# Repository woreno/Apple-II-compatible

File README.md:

# Apple-II-compatible (2021)
Ths is an Apple II compatible built from scratch. As it was made by transfer photo-paper and etching with ferric chloride, and made the traces wider to avoid errors; as result the board didn't fit the A4 copper sheet and memory and slots were made in 2 different boards. 
* The DRAM logic is a bit different from the original.
* System ROM halves are selectable by a switch; one half will run a memory test, another half is Apple II original ROM.
* Character ROM layout is different as pins differs.
* The keyboard and keyboard board were also etched, and theres a ROM that translates the scancodes into ascii - the original had a GY AY-5-3600 chip with a integrated ROM etched from factory.   
* It just has 4 slots instead of 8. Never tested a the slots as i have no Apple II cards. 
Despite this i had planned to assign a number to each of them using a small ROM to store them, and having 7-segment displays to display their number but this as too cumbersome and i stopped the project.

**References** 
 * The Apple II Circuit Description, 1983, Winston D. Gayler
 * Ben Eater's EEPROM arduino programmer

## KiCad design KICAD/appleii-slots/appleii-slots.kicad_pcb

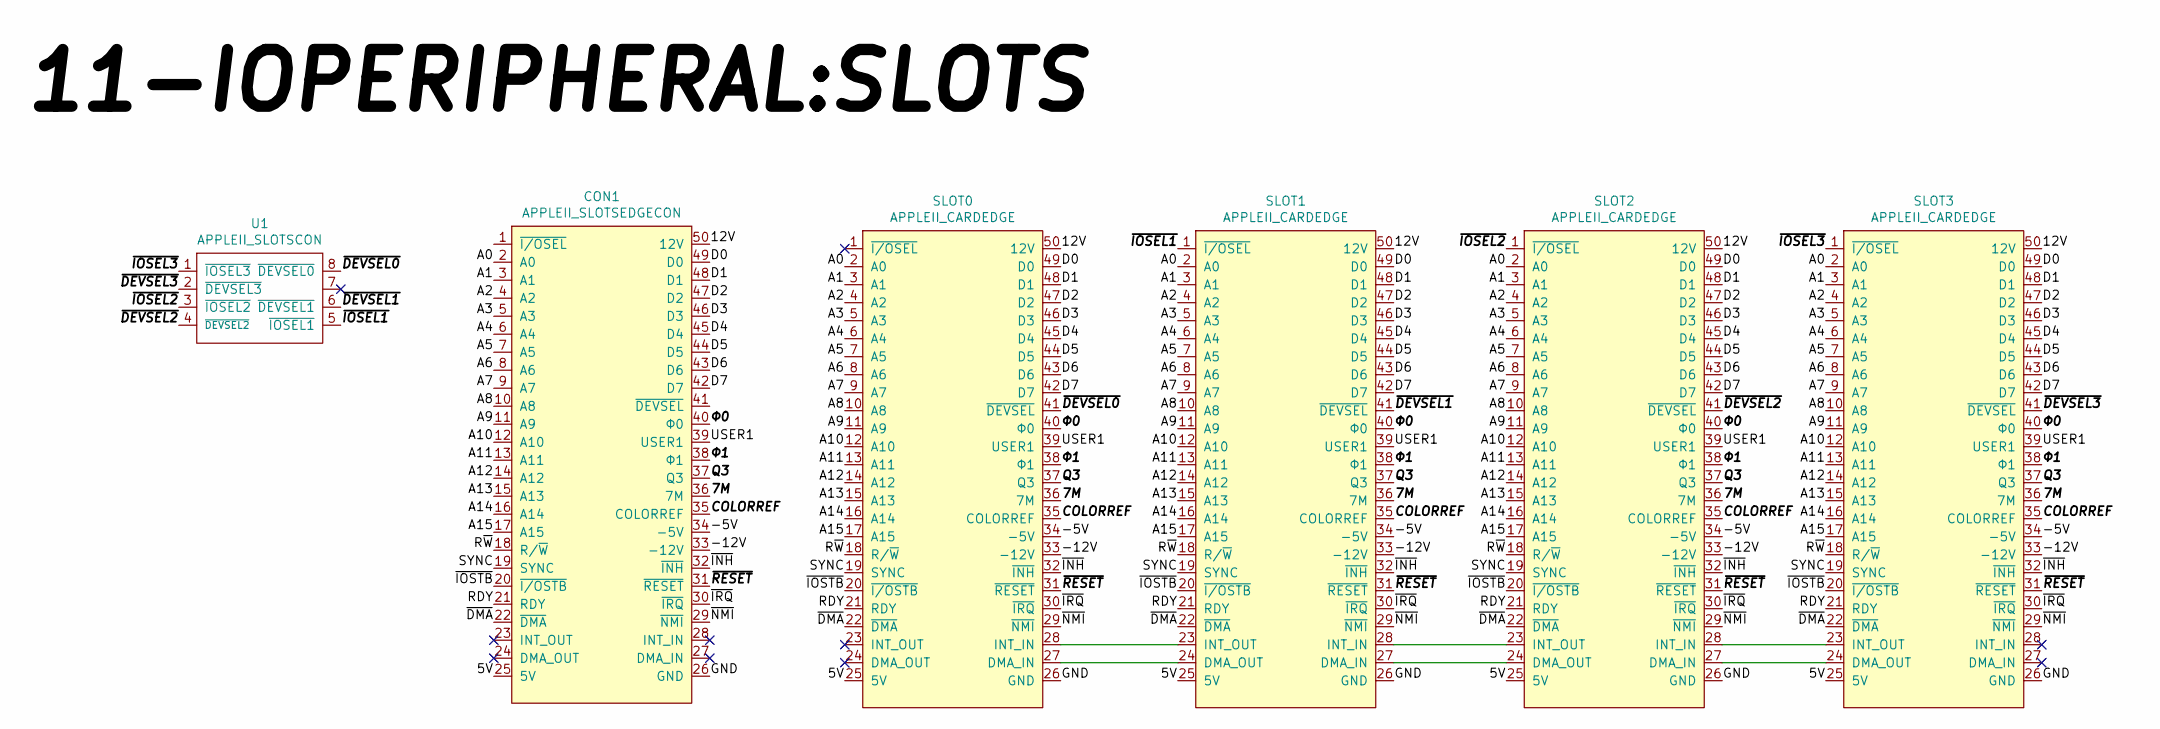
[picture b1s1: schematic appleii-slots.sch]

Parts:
CON1: APPLEII_SLOTSEDGECON; Apple_8bit_edge
SLOT0, SLOT1, SLOT2, SLOT3: APPLEII_CARDEDGE; Conector2x25_Oval_tinny
U1: APPLEII_SLOTSCON; conetor_2x04_P2.54

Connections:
/5V: CON1.25 (5V), SLOT0.25 (5V), SLOT1.25 (5V), SLOT2.25 (5V), SLOT3.25 (5V)
/7M: CON1.36 (7M), SLOT0.36 (7M), SLOT1.36 (7M), SLOT2.36 (7M), SLOT3.36 (7M)
/12V: CON1.50 (12V), SLOT0.50 (12V), SLOT1.50 (12V), SLOT2.50 (12V), SLOT3.50 (12V)
/-5V: CON1.34 (-5V), SLOT0.34 (-5V), SLOT1.34 (-5V), SLOT2.34 (-5V), SLOT3.34 (-5V)
/-12V: CON1.33 (-12V), SLOT0.33 (-12V), SLOT1.33 (-12V), SLOT2.33 (-12V), SLOT3.33 (-12V)
/A0: CON1.2 (A0), SLOT0.2 (A0), SLOT1.2 (A0), SLOT2.2 (A0), SLOT3.2 (A0)
/A1: CON1.3 (A1), SLOT0.3 (A1), SLOT1.3 (A1), SLOT2.3 (A1), SLOT3.3 (A1)
/A2: CON1.4 (A2), SLOT0.4 (A2), SLOT1.4 (A2), SLOT2.4 (A2), SLOT3.4 (A2)
/A3: CON1.5 (A3), SLOT0.5 (A3), SLOT1.5 (A3), SLOT2.5 (A3), SLOT3.5 (A3)
/A4: CON1.6 (A4), SLOT0.6 (A4), SLOT1.6 (A4), SLOT2.6 (A4), SLOT3.6 (A4)
/A5: CON1.7 (A5), SLOT0.7 (A5), SLOT1.7 (A5), SLOT2.7 (A5), SLOT3.7 (A5)
/A6: CON1.8 (A6), SLOT0.8 (A6), SLOT1.8 (A6), SLOT2.8 (A6), SLOT3.8 (A6)
/A7: CON1.9 (A7), SLOT0.9 (A7), SLOT1.9 (A7), SLOT2.9 (A7), SLOT3.9 (A7)
/A8: CON1.10 (A8), SLOT0.10 (A8), SLOT1.10 (A8), SLOT2.10 (A8), SLOT3.10 (A8)
/A9: CON1.11 (A9), SLOT0.11 (A9), SLOT1.11 (A9), SLOT2.11 (A9), SLOT3.11 (A9)
/A10: CON1.12 (A10), SLOT0.12 (A10), SLOT1.12 (A10), SLOT2.12 (A10), SLOT3.12 (A10)
/A11: CON1.13 (A11), SLOT0.13 (A11), SLOT1.13 (A11), SLOT2.13 (A11), SLOT3.13 (A11)
/A12: CON1.14 (A12), SLOT0.14 (A12), SLOT1.14 (A12), SLOT2.14 (A12), SLOT3.14 (A12)
/A13: CON1.15 (A13), SLOT0.15 (A13), SLOT1.15 (A13), SLOT2.15 (A13), SLOT3.15 (A13)
/A14: CON1.16 (A14), SLOT0.16 (A14), SLOT1.16 (A14), SLOT2.16 (A14), SLOT3.16 (A14)
/A15: CON1.17 (A15), SLOT0.17 (A15), SLOT1.17 (A15), SLOT2.17 (A15), SLOT3.17 (A15)
/COLORREF: CON1.35 (COLORREF), SLOT0.35 (COLORREF), SLOT1.35 (COLORREF), SLOT2.35 (COLORREF), SLOT3.35 (COLORREF)
/D0: CON1.49 (D0), SLOT0.49 (D0), SLOT1.49 (D0), SLOT2.49 (D0), SLOT3.49 (D0)
/D1: CON1.48 (D1), SLOT0.48 (D1), SLOT1.48 (D1), SLOT2.48 (D1), SLOT3.48 (D1)
/D2: CON1.47 (D2), SLOT0.47 (D2), SLOT1.47 (D2), SLOT2.47 (D2), SLOT3.47 (D2)
/D3: CON1.46 (D3), SLOT0.46 (D3), SLOT1.46 (D3), SLOT2.46 (D3), SLOT3.46 (D3)
/D4: CON1.45 (D4), SLOT0.45 (D4), SLOT1.45 (D4), SLOT2.45 (D4), SLOT3.45 (D4)
/D5: CON1.44 (D5), SLOT0.44 (D5), SLOT1.44 (D5), SLOT2.44 (D5), SLOT3.44 (D5)
/D6: CON1.43 (D6), SLOT0.43 (D6), SLOT1.43 (D6), SLOT2.43 (D6), SLOT3.43 (D6)
/D7: CON1.42 (D7), SLOT0.42 (D7), SLOT1.42 (D7), SLOT2.42 (D7), SLOT3.42 (D7)
/GND: CON1.26 (GND), SLOT0.26 (GND), SLOT1.26 (GND), SLOT2.26 (GND), SLOT3.26 (GND)
/Q3: CON1.37 (Q3), SLOT0.37 (Q3), SLOT1.37 (Q3), SLOT2.37 (Q3), SLOT3.37 (Q3)
/RDY: CON1.21 (RDY), SLOT0.21 (RDY), SLOT1.21 (RDY), SLOT2.21 (RDY), SLOT3.21 (RDY)
/R~W: CON1.18 (R/~W), SLOT0.18 (R/~W), SLOT1.18 (R/~W), SLOT2.18 (R/~W), SLOT3.18 (R/~W)
/SYNC: CON1.19 (SYNC), SLOT0.19 (SYNC), SLOT1.19 (SYNC), SLOT2.19 (SYNC), SLOT3.19 (SYNC)
/USER1: CON1.39 (USER1), SLOT0.39 (USER1), SLOT1.39 (USER1), SLOT2.39 (USER1), SLOT3.39 (USER1)
/~DEVSEL0: SLOT0.41 (~DEVSEL), U1.8 (~DEVSEL0)
/~DEVSEL1: SLOT1.41 (~DEVSEL), U1.6 (~DEVSEL1)
/~DEVSEL2: SLOT2.41 (~DEVSEL), U1.4 (~DEVSEL2)
/~DEVSEL3: SLOT3.41 (~DEVSEL), U1.2 (~DEVSEL3)
/~DMA: CON1.22 (~DMA), SLOT0.22 (~DMA), SLOT1.22 (~DMA), SLOT2.22 (~DMA), SLOT3.22 (~DMA)
/~INH: CON1.32 (~INH), SLOT0.32 (~INH), SLOT1.32 (~INH), SLOT2.32 (~INH), SLOT3.32 (~INH)
/~IOSEL1: SLOT1.1 (~I/OSEL), U1.5 (~IOSEL1)
/~IOSEL2: SLOT2.1 (~I/OSEL), U1.3 (~IOSEL2)
/~IOSEL3: SLOT3.1 (~I/OSEL), U1.1 (~IOSEL3)
/~IOSTB: CON1.20 (~I/OSTB), SLOT0.20 (~I/OSTB), SLOT1.20 (~I/OSTB), SLOT2.20 (~I/OSTB), SLOT3.20 (~I/OSTB)
/~IRQ: CON1.30 (~IRQ), SLOT0.30 (~IRQ), SLOT1.30 (~IRQ), SLOT2.30 (~IRQ), SLOT3.30 (~IRQ)
/~NMI: CON1.29 (~NMI), SLOT0.29 (~NMI), SLOT1.29 (~NMI), SLOT2.29 (~NMI), SLOT3.29 (~NMI)
/~RESET: CON1.31 (~RESET), SLOT0.31 (~RESET), SLOT1.31 (~RESET), SLOT2.31 (~RESET), SLOT3.31 (~RESET)
/Φ0: CON1.40 (Φ0), SLOT0.40 (Φ0), SLOT1.40 (Φ0), SLOT2.40 (Φ0), SLOT3.40 (Φ0)
/Φ1: CON1.38 (Φ1), SLOT0.38 (Φ1), SLOT1.38 (Φ1), SLOT2.38 (Φ1), SLOT3.38 (Φ1)
unnamed: SLOT0.27 (DMA_IN), SLOT1.24 (DMA_OUT)
unnamed: SLOT0.28 (INT_IN), SLOT1.23 (INT_OUT)
unnamed: SLOT1.27 (DMA_IN), SLOT2.24 (DMA_OUT)
unnamed: SLOT1.28 (INT_IN), SLOT2.23 (INT_OUT)
unnamed: SLOT2.27 (DMA_IN), SLOT3.24 (DMA_OUT)
unnamed: SLOT2.28 (INT_IN), SLOT3.23 (INT_OUT)

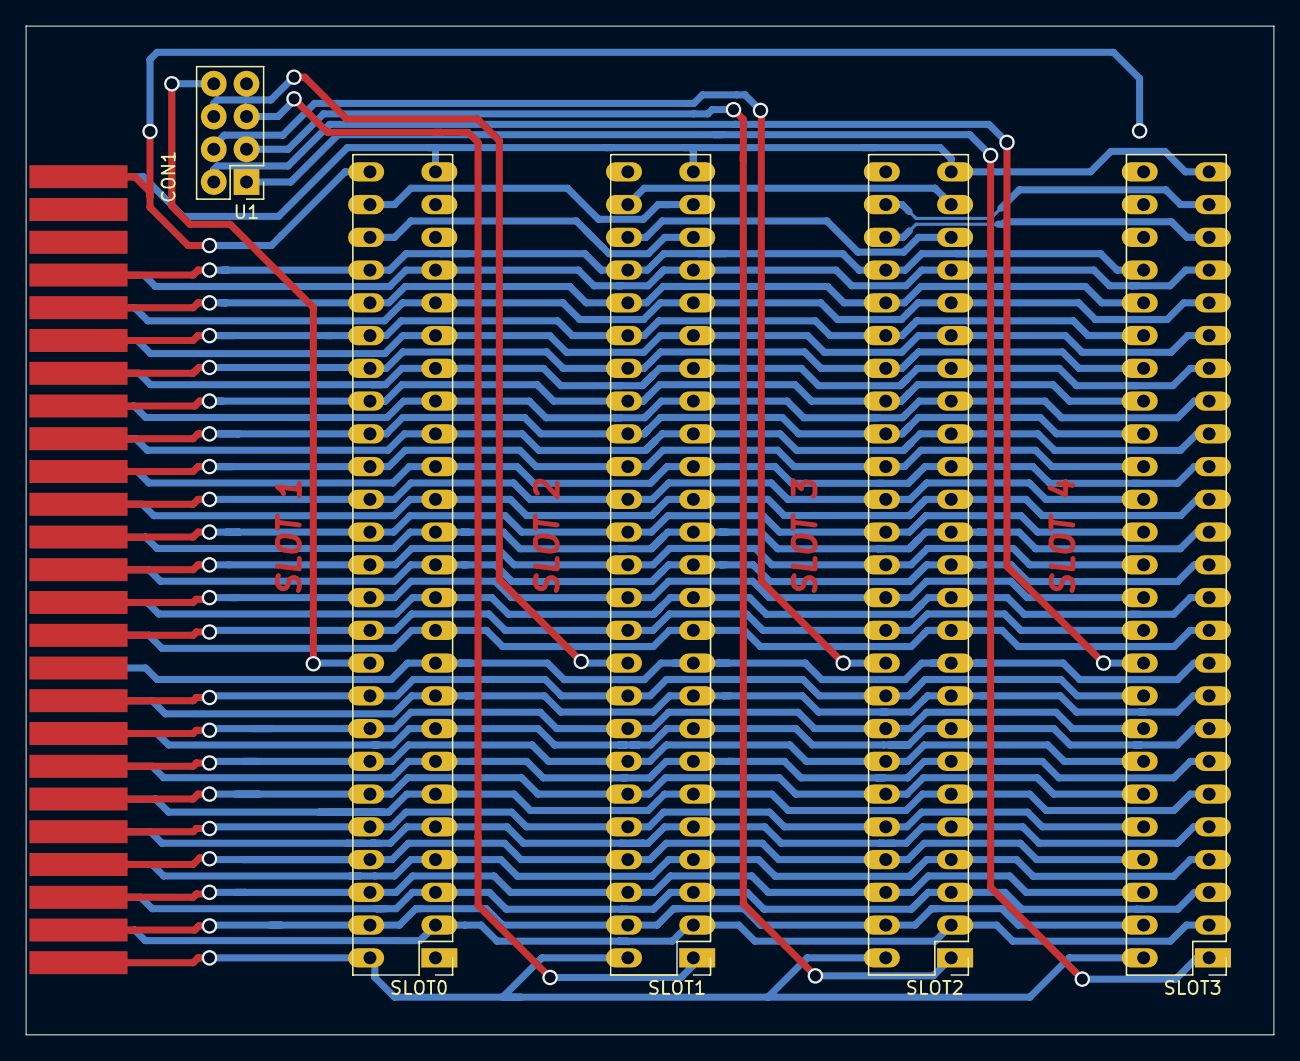
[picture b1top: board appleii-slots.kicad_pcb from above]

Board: 2 copper layers, 96.8 x 78.2 mm, 6 parts (0 on the bottom side), 57 nets.

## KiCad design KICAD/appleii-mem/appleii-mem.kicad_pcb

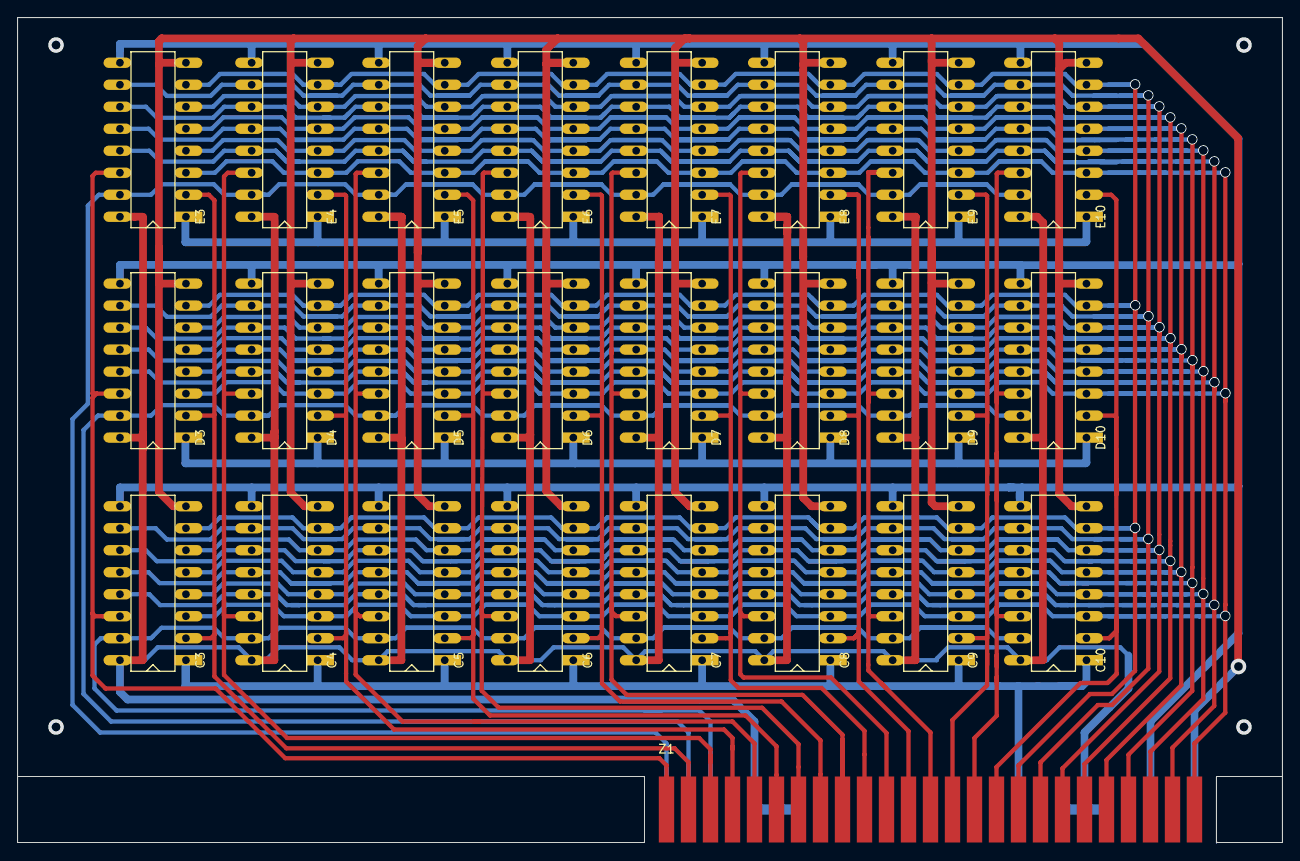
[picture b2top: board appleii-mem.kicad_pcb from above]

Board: 2 copper layers, 146.0 x 95.3 mm, 25 parts (0 on the bottom side), 32 nets.

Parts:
C3, C4, C5, C6, C7, C8, C9, C10: DRAM_4116_2KB_DIP16; standard_DIP_16OvalPins
D3, D4, D5, D6, D7, D8, D9, D10: DRAM_4116_2KB_DIP16; standard_DIP_16OvalPins
E3, E4, E5, E6, E7, E8, E9, E10: DRAM_4116_2KB_DIP16; standard_DIP_16OvalPins
Z1: APPLEII_MEMCON; Apple_8bit_edge

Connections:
/5V: C3.9, C4.9, C5.9, C6.9, C7.9, C8.9, C9.9, C10.9, D3.9, D4.9, D5.9, D6.9, D7.9, D8.9, D9.9, D10.9, E3.9, E4.9, E5.9, E6.9, E7.9, E8.9, E9.9, E10.9, Z1.3
/12V: C3.8, C4.8, C5.8, C6.8, C7.8, C8.8, C9.8, C10.8, D3.8, D4.8, D5.8, D6.8, D7.8, D8.8, D9.8, D10.8, E3.8, E4.8, E5.8, E6.8, E7.8, E8.8, E9.8, E10.8, Z1.1
/-5V: C3.1, C4.1, C5.1, C6.1, C7.1, C8.1, C9.1, C10.1, D3.1, D4.1, D5.1, D6.1, D7.1, D8.1, D9.1, D10.1, E3.1, E4.1, E5.1, E6.1, E7.1, E8.1, E9.1, E10.1, Z1.9
/D0: C3.2, D3.2, E3.2, Z1.27
/D1: C4.2, D4.2, E4.2, Z1.29
/D2: C5.2, D5.2, E5.2, Z1.31
/D3: C6.2, D6.2, E6.2, Z1.33
/D4: C7.2, D7.2, E7.2, Z1.35
/D5: C8.2, D8.2, E8.2, Z1.37
/D6: C9.2, D9.2, E9.2, Z1.39
/D7: C10.2, D10.2, E10.2, Z1.41
/DO0: C3.14, D3.14, E3.14, Z1.26
/DO1: C4.14, D4.14, E4.14, Z1.28
/DO2: C5.14, D5.14, E5.14, Z1.30
/DO3: C6.14, D6.14, E6.14, Z1.32
/DO4: C7.14, D7.14, E7.14, Z1.34
/DO5: C8.14, D8.14, E8.14, Z1.36
/DO6: C9.14, D9.14, E9.14, Z1.38
/DO7: C10.14, D10.14, E10.14, Z1.40
/GND: C3.16, C4.16, C5.16, C6.16, C7.16, C8.16, C9.16, C10.16, D3.16, D4.16, D5.16, D6.16, D7.16, D8.16, D9.16, D10.16, E3.16, E4.16, E5.16, E6.16, E7.16, E8.16, E9.16, E10.16, Z1.5, Z1.6, Z1.7, Z1.19, Z1.20, Z1.21
/RA0: C3.5, C4.5, C5.5, C6.5, C7.5, C8.5, C9.5, C10.5, D3.5, D4.5, D5.5, D6.5, D7.5, D8.5, D9.5, D10.5, E3.5, E4.5, E5.5, E6.5, E7.5, E8.5, E9.5, E10.5, Z1.46
/RA1: C3.7, C4.7, C5.7, C6.7, C7.7, C8.7, C9.7, C10.7, D3.7, D4.7, D5.7, D6.7, D7.7, D8.7, D9.7, D10.7, E3.7, E4.7, E5.7, E6.7, E7.7, E8.7, E9.7, E10.7, Z1.42
/RA2: C3.6, C4.6, C5.6, C6.6, C7.6, C8.6, C9.6, C10.6, D3.6, D4.6, D5.6, D6.6, D7.6, D8.6, D9.6, D10.6, E3.6, E4.6, E5.6, E6.6, E7.6, E8.6, E9.6, E10.6, Z1.44
/RA3: C3.12, C4.12, C5.12, C6.12, C7.12, C8.12, C9.12, C10.12, D3.12, D4.12, D5.12, D6.12, D7.12, D8.12, D9.12, D10.12, E3.12, E4.12, E5.12, E6.12, E7.12, E8.12, E9.12, E10.12, Z1.47
/RA4: C3.11, C4.11, C5.11, C6.11, C7.11, C8.11, C9.11, C10.11, D3.11, D4.11, D5.11, D6.11, D7.11, D8.11, D9.11, D10.11, E3.11, E4.11, E5.11, E6.11, E7.11, E8.11, E9.11, E10.11, Z1.45
/RA5: C3.10, C4.10, C5.10, C6.10, C7.10, C8.10, C9.10, C10.10, D3.10, D4.10, D5.10, D6.10, D7.10, D8.10, D9.10, D10.10, E3.10, E4.10, E5.10, E6.10, E7.10, E8.10, E9.10, E10.10, Z1.43
/RA6: C3.13, C4.13, C5.13, C6.13, C7.13, C8.13, C9.13, C10.13, D3.13, D4.13, D5.13, D6.13, D7.13, D8.13, D9.13, D10.13, E3.13, E4.13, E5.13, E6.13, E7.13, E8.13, E9.13, E10.13, Z1.49
/~CAS_C: C3.15, C4.15, C5.15, C6.15, C7.15, C8.15, C9.15, C10.15, Z1.23
/~CAS_D: D3.15, D4.15, D5.15, D6.15, D7.15, D8.15, D9.15, D10.15, Z1.24
/~CAS_E: E3.15, E4.15, E5.15, E6.15, E7.15, E8.15, E9.15, E10.15, Z1.25
/~MEMWR: C3.3, C4.3, C5.3, C6.3, C7.3, C8.3, C9.3, C10.3, D3.3, D4.3, D5.3, D6.3, D7.3, D8.3, D9.3, D10.3, E3.3, E4.3, E5.3, E6.3, E7.3, E8.3, E9.3, E10.3, Z1.50
/~RAS: C3.4, C4.4, C5.4, C6.4, C7.4, C8.4, C9.4, C10.4, D3.4, D4.4, D5.4, D6.4, D7.4, D8.4, D9.4, D10.4, E3.4, E4.4, E5.4, E6.4, E7.4, E8.4, E9.4, E10.4, Z1.48

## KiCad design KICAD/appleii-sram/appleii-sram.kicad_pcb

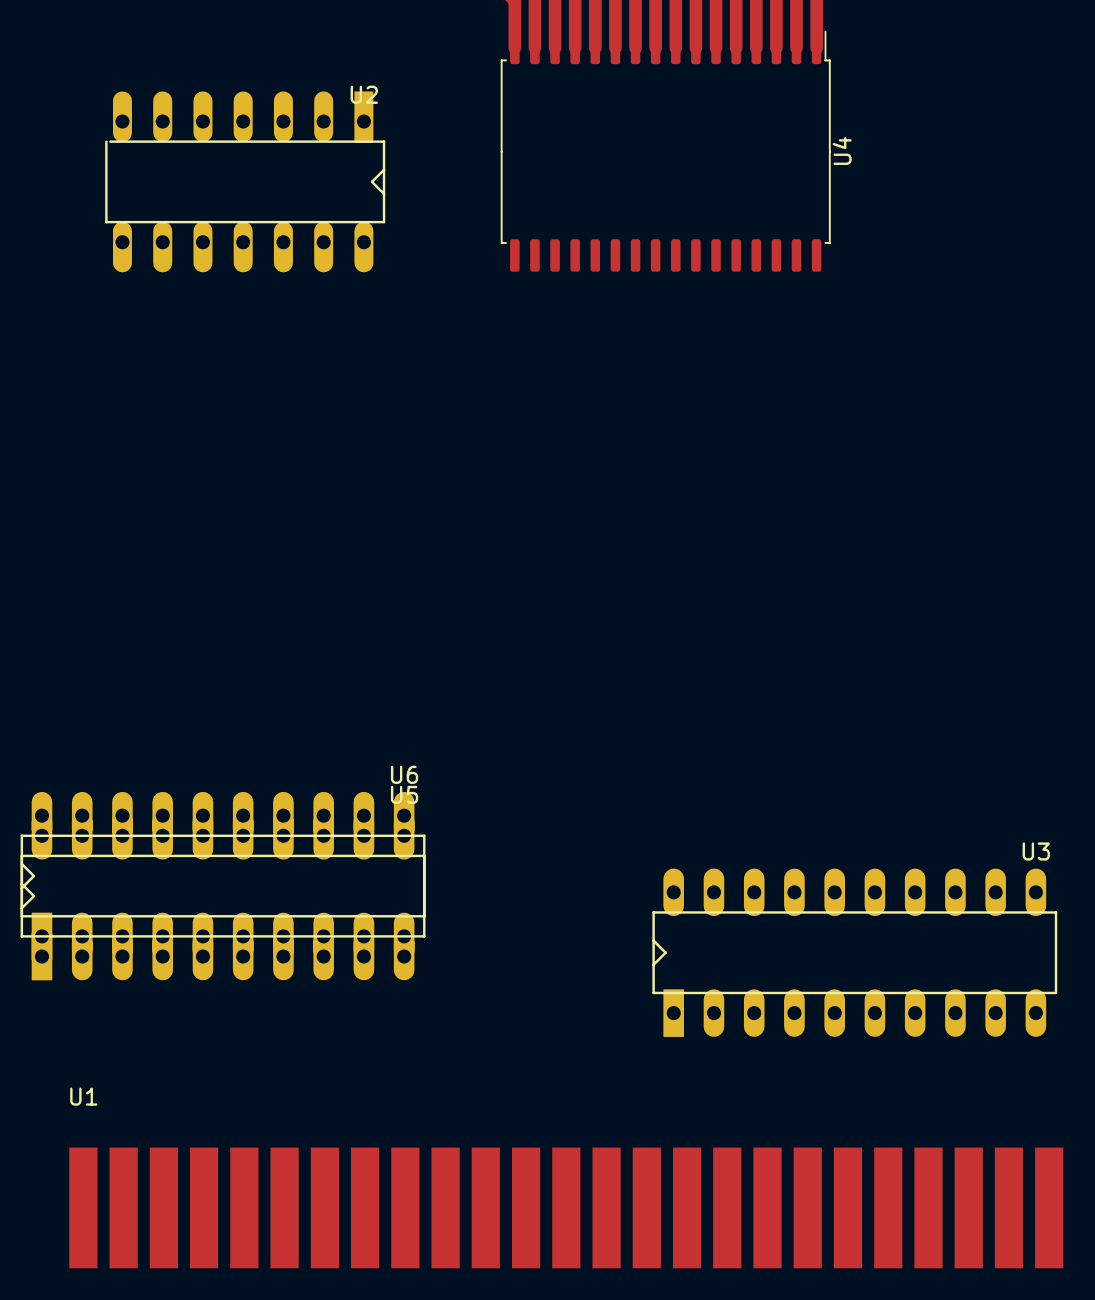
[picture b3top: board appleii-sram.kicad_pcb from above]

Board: 2 copper layers, 6 parts (0 on the bottom side), 47 nets.

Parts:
U1: APPLEII_MEMCON; Apple_8bit_edge
U2: 74LS04; standard_DIP_14OvalPins
U3: 74LS574; standard_DIP_20pins_thin_body
U4: AS6C4008-55PCN; SSOP-32_11.305x20.495mm_P1.27mm
U5, U6: 74LS245; standard_DIP_20pins_thin_body

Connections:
/A0: U1.2, U3.3, U4.5
/A0': U3.18, U4.12
/A1: U1.3, U3.4, U4.27
/A1': U3.17, U4.11
/A2: U1.4, U3.5, U4.26
/A2': U3.16, U4.10
/A3: U1.5, U3.6, U4.23
/A3': U3.15, U4.9
/A4: U1.6, U3.7, U4.25
/A4': U3.14, U4.8
/A5: U1.7, U3.8, U4.4
/A5': U3.13, U4.7
/A6: U1.8, U3.9, U4.28
/A6': U3.12, U4.6
/D0: U1.49, U6.2
/D0': U4.13, U5.18, U6.18
/D1: U1.48, U6.3
/D1': U4.14, U5.17, U6.17
/D2: U1.47, U6.4
/D2': U4.15, U5.16, U6.16
/D3: U1.46, U6.5
/D3': U4.17, U5.15, U6.15
/D4: U1.45, U6.6
/D4': U4.18, U5.14, U6.14
/D5: U1.44, U6.7
/D5': U4.19, U5.13, U6.13
/D6: U1.43, U6.8
/D6': U4.20, U5.12, U6.12
/D7: U1.42, U6.9
/D7': U4.21, U5.11, U6.11
/Do0: U1.9, U5.2
/Do1: U1.10, U5.3
/Do2: U1.11, U5.4
/Do3: U1.12, U5.5
/Do4: U1.13, U5.6
/Do5: U1.14, U5.7
/Do6: U1.15, U5.8
/Do7: U1.16, U5.9
/GND: U1.26, U3.10, U4.1, U4.16, U4.22, U4.24, U4.30, U6.1, U6.10
/RAS: U2.2, U3.11
/VCC: U1.25, U3.20, U4.32, U5.20
/WRITE: U2.12, U5.19
/~CAS0: U1.20, U4.3
/~CAS1: U1.21, U4.31
/~CAS2: U1.22, U4.2
/~RAS: U1.19, U2.1
/~WRITE: U1.18, U2.13, U4.29, U6.19

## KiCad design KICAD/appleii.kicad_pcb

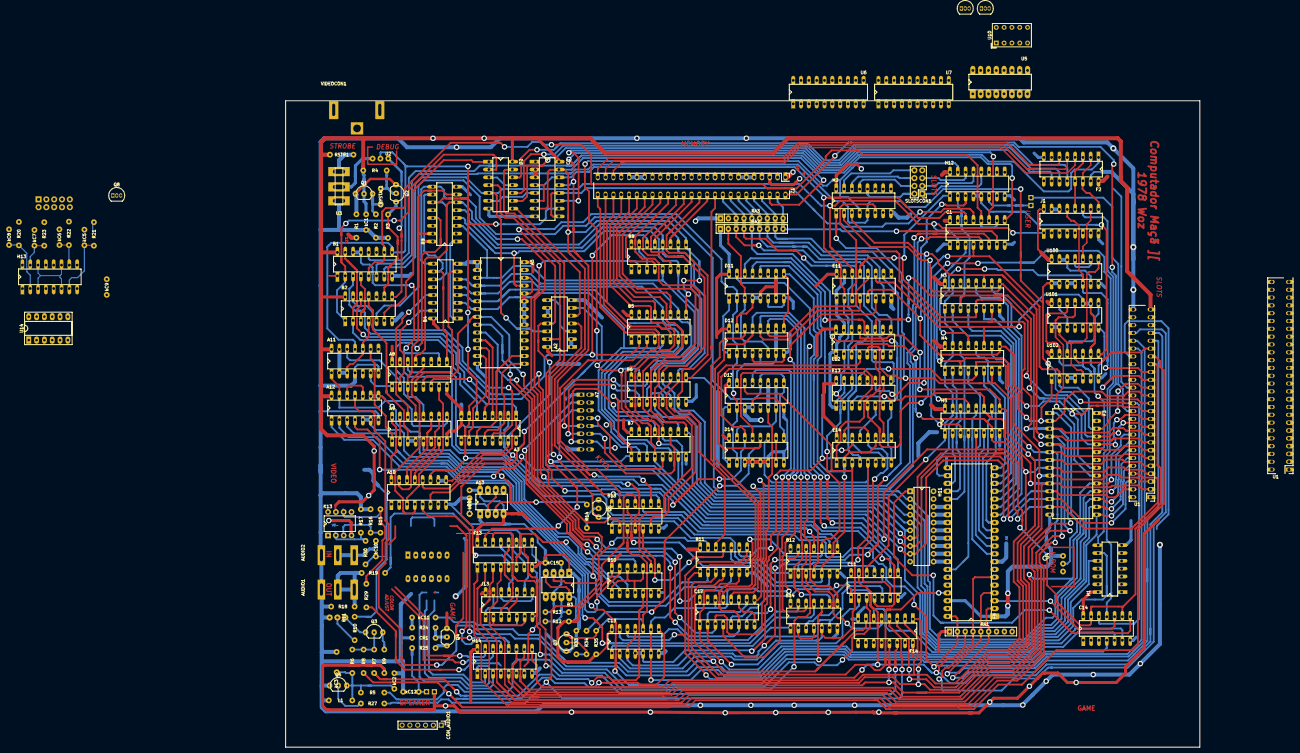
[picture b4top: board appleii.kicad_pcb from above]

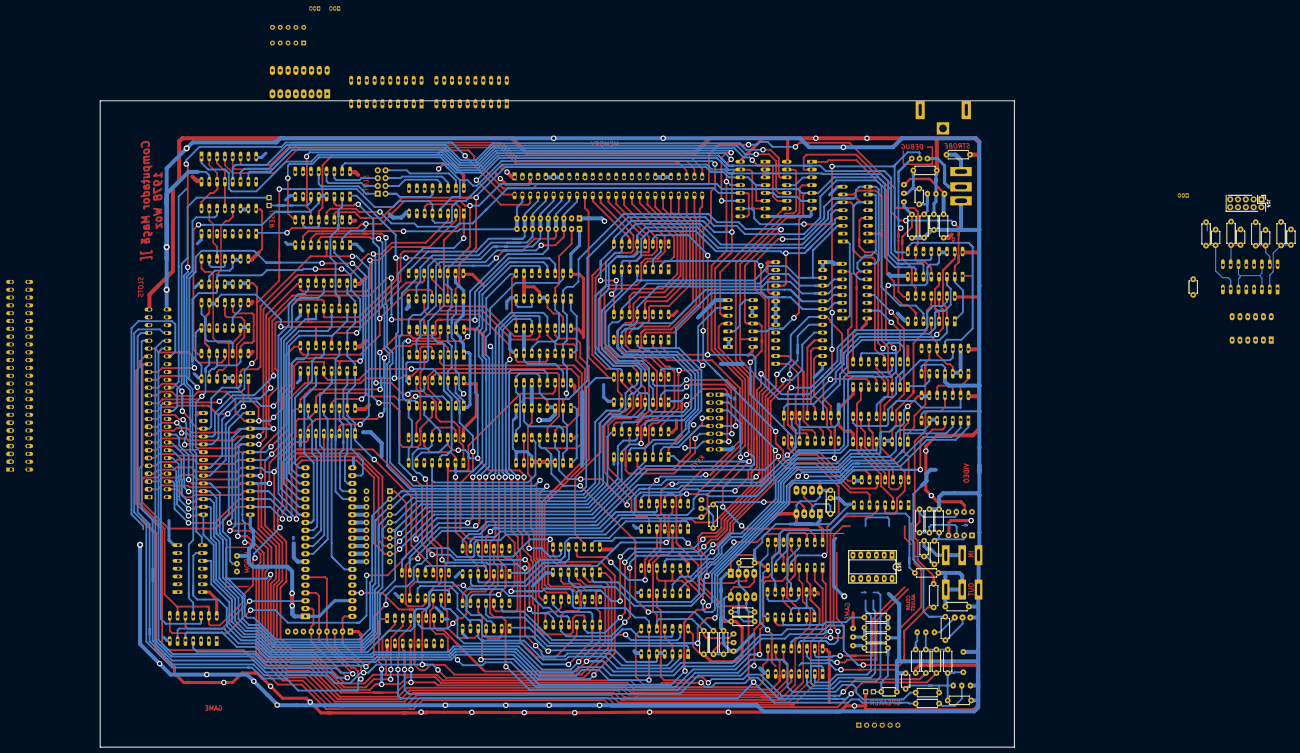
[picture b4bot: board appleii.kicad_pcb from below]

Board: 2 copper layers, 297.0 x 210.0 mm, 141 parts (2 on the bottom side), 324 nets.

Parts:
A2: 74LS00; standard_DIP_14OvalPins
A3: 74LS166; standard_DIP_16OvalPins
A5: PPROM_28C65_256; standard_DIP_28pins_thin_doubleBody
A7: APPLEII_KEYBCON; Conector2x8_Oval
A8: 74LS257_RD; standard_DIP_16OvalPins
A9: 74LS151; standard_DIP_16OvalPins
A10: 74LS194; standard_DIP_16OvalPins
A11: 74LS74; standard_DIP_14OvalPins
A12: 74LS02; standard_DIP_14OvalPins
A13: 555; standard_DIP_8pins
AUDIO1, AUDIO2: TS; TS - mono jack MJ3502N
B1: 74_175; standard_DIP_16OvalPins
B2: 74LS86; standard_DIP_14OvalPins
B3: 555; standard_DIP_8pins
B4, B9: 74LS194; standard_DIP_16OvalPins
B5, B8: 74LS174; standard_DIP_16OvalPins
B6, B7: 74LS257_RD; standard_DIP_16OvalPins
B10: 74LS74; standard_DIP_14OvalPins
B11: 74LS08; standard_DIP_14OvalPins
B12: 74LS11; standard_DIP_14OvalPins
B13, B14: 74LS02; standard_DIP_14OvalPins
C1: 74_153; standard_DIP_16OvalPins
C2: 74S195; standard_DIP_16OvalPins
C11: 74LS04; standard_DIP_14OvalPins
C12: 74_257; standard_DIP_16OvalPins
C13: 74LS51; standard_DIP_14OvalPins
C14: 74LS32; standard_DIP_14OvalPins
CON_AUDIO1: Conn_01x06_Female; PinHeader_1x06_P2.54mm_Vertical
CR1: 1N914; standard_2pins
CRYSTAL1: 14.31818M; standard_2pins_half
D2: 74LS20; standard_DIP_14OvalPins
D11, D12, D13, D14: 74LS161; standard_DIP_16OvalPins
E11, E12, E13: 74LS153; standard_DIP_16OvalPins
E14: 74LS283; standard_DIP_16OvalPins
F2: 74LS139; standard_DIP_16OvalPins
F3: PPROM_28C65_256; standard_DIP_28pins_thin_doubleBody
F13: 74LS138; standard_DIP_16OvalPins
F14: 74LS259; standard_DIP_16OvalPins
H1: 74LS08; standard_DIP_14OvalPins
H2, H12: 74LS138; standard_DIP_16OvalPins
H3, H4, H5: 8T97_HEXBUF; standard_DIP_16OvalPins
H8: CPU_6502; standard_DIP_40pins_doubleBody
H11: 74LS245; standard_DIP_20pins
H13: 558; standard_DIP_16OvalPins
H14: 74LS251; standard_DIP_16OvalPins
J1: 74_257; standard_DIP_16OvalPins
J13: 74LS74; standard_DIP_14OvalPins
J14: APPLEII_GAMECON; conetor_2x05_P2.54_toDB9
JP1: Jumper; jumper_set_1
K13: OpAmp_741; LM386
L1: 27u; standard_2pins
Q1, Q2: 2N3906; TO-92_Inline
Q3, Q5, Q6, Q7, Q8, Q9, Q10: 2N3904; TO-92_Inline
Q4: MPSA13; TO-92_Inline
R1: 330; standard_2pins
R2, R4: 47; standard_2pins
R3: 150; standard_2pins
R5, R14: 1K; standard_2pins
R6: 2.7K; standard_2pins
R7, R35: 1.5K; standard_2pins
R8, R33, R34: 2K; standard_2pins
R9: 10; standard_2pins
R10, R25: 27; standard_2pins
R11: 200; trimpot - 3 pin standard
R12, R16, R17, R19, R29, R30: 12K; standard_2pins
R13: 3.3M; standard_2pins
R15: 1M; standard_2pins
R18, R20, R21, R22, R23: 100; standard_2pins
R24: 47K; standard_2pins
R26: 2.2M; standard_2pins
R27: 4.7K; standard_2pins
RA1, RA2, RA3: 1K; R_Array_SIP9
RSTR1: R; standard_2pins
SLOTSCON1: APPLEII_SLOTSCON; conetor_2x04_P2.54
SPK1: 8; jumper_set_1
U1, U1#2: APPLEII_CARDEDGE; Conector2x25_Oval_0.65_rightangle
U2: manual_clock_onoff; mini_flipswitch2.54
U3: manual_clock_strobe; flipSwitch3
U4: flipSwitch; mini_flipswitch2.54
U5: 74LS175; standard_DIP_16Pins
U6, U7: 74LS244; standard_DIP_20pins_thin_body
U10: HDSP-7503; HDSP-A151
U13, U14: APPLEII_DIGITAL_GAMEPAD_FEMALE; DIP-12_W7.62mm_Socket_LongPads
U100, U101: 74LS00; standard_DIP_14OvalPins
U102: 74LS32; standard_DIP_14OvalPins
VIDEOCON1: COMP. VIDEO OUT; RCA-phono jack
Z1: APPLEII_MEMCON; Conector2x25_Oval_0.65_rightangle
kC1, kC4, kC9, kC10, kC12, kC15: 0.1u; standard_2pins_half
kC2: 47p; standard_2pins_half
kC3: 5-50p; standard_small_cap_trimmer
kC5, kC6, kC7, kC8: 22n; standard_2pins_half
kC11: 0.1u; standard_2pins

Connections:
/5V: A2.14, A3.16, A5.28, A7.1, A8.16, A9.16, A10.16, A11.14, A12.14, A13.4, A13.8, B1.16, B2.14, B3.4, B3.8, B4.16, B5.16, B7.16, B8.16, B9.16, B10.14, B11.14, B12.14, B13.14, B14.14, C1.16, C2.16, C11.14, C12.16, C13.14, C14.14, D2.14, D11.16, D12.16, D13.16, D14.16, E12.16, E13.16, E14.16, F2.16, F3.28, F13.16, F14.16, H1.14, H2.16, H12.16, H13.5, H13.13, H14.16, J1.16, J13.14, J14.2, K13.7, Q1.2, R4.2, R9.1, R12.1, R26.1, R35.2, RA1.1, RA2.1, RSTR1.2, U1.25, U1#2.25, U5.16, U13.6, U14.6, U100.14, U101.14, U102.14, Z1.3, kC1.1
/7M: A3.6, B1.15, B2.2, U1.36, U1#2.36
/12V: R1.1, Z1.1
/14M: A3.7, A10.11, A11.11, B1.9, B4.11, B9.11, B10.3, C2.10, U2.2
/14M_OUT: B2.8, U2.3
/-5V: K13.4, Z1.9
/A0: E13.3, F3.10, F14.13, H5.11, H14.11, U1.2, U1#2.2
/A1: E13.13, F3.9, F14.1, H4.5, H14.10, U1.3, U1#2.3
/A2: E12.3, F3.8, F14.2, H5.7, H14.9, U1.4, U1#2.4
/A3: E12.13, F3.7, F14.3, H5.9, U1.5, U1#2.5
/A4: E12.5, F3.6, F13.1, H2.1, H4.7, U1.6, U1#2.6
/A5: E13.5, F3.5, F13.2, H2.2, H3.9, U1.7, U1#2.7
/A6: E13.11, F3.4, F13.3, H2.3, H3.11, U1.8, U1#2.8
/A7: E11.3, F3.3, F13.4, H2.6, H3.7, U1.9, U1#2.9
/A8: E11.13, F3.25, H3.5, H12.1, U1.10, U1#2.10
/A9: E12.11, F3.24, H3.3, H12.2, U1.11, U1#2.11
/A10: E11.5, F3.21, H4.9, H12.3, U1.12, U1#2.12
/A11: E11.11, F3.23, H4.11, U1.13, U1#2.13, U101.9, U101.10, U102.9
/A12: C1.3, F3.2, H4.3, U1.14, U1#2.14, U102.1
/A13: C1.4, F3.26, H5.3, U1.15, U1#2.15, U102.2
/A14: H5.13, J1.10, U1.16, U1#2.16, U100.10
/A15: H4.13, J1.13, U1.17, U1#2.17, U100.5
/AX: C1.14, C2.4, C2.6, C2.14, E11.2, E12.2, E13.2
/AXCAS: A2.13, B12.11, B13.10, D2.4
/B4_Q0: A8.2, A11.12, B4.15
/B9_Q0: A8.3, A9.13, B9.7, B9.15
/BLANKING: A10.5, C14.6
/CASSETE_DIGITAL_INPUT: CON_AUDIO1.4, CON_AUDIO1.5, R29.2
/CASSETE_OUT_CLK: F13.13, J13.11, Q10.2
/CLRSTB: A12.2, C11.4
/COLORBURST: L1.1, Q6.3, R5.1, R6.2, kC2.1, kC3.1
/COLORREF: B1.3, B13.2, U1.35, U1#2.35
/CON_CPU_OUT: CON_AUDIO1.3, J13.9, R19.1
/CON_SPK: CON_AUDIO1.1, CON_AUDIO1.2, J13.5, kC11.2
/D0: B7.4, F3.11, H11.9, U1.49, U1#2.49, Z1.27
/D1: B7.7, F3.12, H11.8, U1.48, U1#2.48, Z1.29
/D2: B7.12, F3.13, H11.7, U1.47, U1#2.47, Z1.31
/D3: B7.9, F3.15, H11.6, U1.46, U1#2.46, Z1.33
/D4: B6.4, F3.16, H11.5, U1.45, U1#2.45, Z1.35
/D5: B6.12, F3.17, H11.4, U1.44, U1#2.44, Z1.37
/D6: B6.7, F3.18, H11.3, U1.43, U1#2.43, Z1.39
/D7: B6.9, F3.19, H11.2, H14.5, U1.42, U1#2.42, Z1.41
/DO0: B5.4, Z1.26
/DO1: B5.6, Z1.28
/DO2: B5.13, Z1.30
/DO3: B5.11, Z1.32
/DO4: B8.4, Z1.34
/DO5: B8.6, Z1.36
/DO6: B8.13, U5.12, Z1.38
/DO7: B8.11, Z1.40
/FROM_LATCHB8_Q0: A12.8, A12.9, B8.2, B11.5
/GAME_OUT0: H13.1, H14.15, U13.1, U14.1
/GAME_OUT1: H13.8, H14.12, U13.2, U14.2
/GAME_OUT2: H13.9, H14.13, U13.7, U14.7
/GAME_OUT3: H13.16, H14.14, U13.8, U14.8
/GAME_RESET_TIMERS: F13.7, H13.3, H13.6, H13.11, H13.14, U13.3, U14.3
/GAME_SW0: H14.3, J14.7, U13.10, U14.10
/GAME_SW1: H14.2, J14.1, U13.11, U14.11
/GAME_SW2: H14.1, J14.6, U13.12, U14.12
/GAME_TIM0: H13.2, R20.1, kC8.1
/GAME_TIM1: H13.7, R21.1, kC5.1
/GAME_TIM2: H13.10, R22.1, kC6.1
/GAME_TIM3: H13.15, R23.1, kC7.1
/GND: A2.1, A2.2, A2.7, A2.9, A2.10, A3.3, A3.8, A3.14, A5.1, A5.2, A5.14, A5.20, A5.21, A5.22, A5.23, A5.24, A5.26, A7.8, A8.8, A8.15, A9.8, A10.8, A11.4, A11.7, A12.7, A13.1, AUDIO1.S, AUDIO2.S, B1.8, B2.7, B2.10, B3.1, B4.8, B5.8, B6.8, B7.8, B8.8, B9.8, B10.7, B11.7, B12.7, B13.7, B14.7, C1.1, C1.8, C1.15, C2.2, C2.3, C2.8, C11.7, C12.8, C12.11, C12.15, C13.7, C14.7, CR1.2, D2.7, D11.6, D11.8, D12.4, D12.8, D13.3, D13.4, D13.8, D14.3, D14.4, D14.5, D14.6, D14.8, E11.1, E11.8, E11.15, E12.1, E12.8, E12.15, E13.1, E13.8, E13.15, E14.8, F2.8, F2.15, F3.14, F3.22, F13.8, F14.8, H1.7, H2.8, H3.8, H4.8, H5.8, H8.1, H8.21, H8.38, H11.10, H11.19, H12.8, H13.12, H14.8, J1.8, J1.14, J1.15, J13.7, J14.3, L1.2, Q4.1, Q5.1, Q6.1, Q7.1, Q8.1, Q9.1, Q10.1, R2.2, R3.2, R11.3, R16.2, R17.2, R18.1, R33.1, RA3.1, U1.26, U1#2.26, U3.1, U4.3, U5.8, U13.4, U14.4, U100.7, U101.7, U102.7, VIDEOCON1.2, Z1.5, Z1.6, Z1.7, Z1.19, Z1.20, Z1.21, kC1.2, kC2.2, kC3.2, kC4.2, kC5.2, kC6.2, kC7.2, kC8.2, kC9.2, kC12.2, kC15.2
/H0: A8.14, D14.14, E13.4
/H1: D14.13, E13.12
/H2: D14.12, E12.4, R34.1
/H3: B12.2, C13.3, C13.11, D14.11, E14.5
/H4: B14.5, C13.2, D13.14, E14.3
/H5: B14.6, C11.5, C13.4, C13.5, D13.13
/HBL: B12.13, C12.14, C13.6, C13.9, C14.5
/HIRES: B11.6, C12.1, H1.9
/HIRESMODE: A12.11, B11.4, F14.7
/KEY0: A7.12, B7.2
/KEY1: A7.13, B7.5
/KEY2: A7.10, B7.14
/KEY3: A7.11, B7.11
/KEY4: A7.6, B6.2
/KEY5: A7.5, B6.14
/KEY6: A7.7, B6.5
/KEY7: B6.11, B10.9
/LD0: A5.7, B4.3, B5.5, B7.3
/LD1: A5.6, B4.4, B5.7, B7.6
/LD2: A5.5, B4.5, B5.12, B7.13
/LD3: A5.4, B4.6, B5.10, B7.10
/LD4: A5.3, B6.3, B8.5, B9.3
/LD5: A5.25, B6.13, B8.7, B9.4
/LD6: B6.6, B8.12, B9.5, B11.12, U5.10
/LD7: A8.13, B6.10, B8.10, B9.6, B13.6
/LD194: A10.9, A10.10, B4.9, B9.9, B12.8
/M5V: U1.34, U1#2.34
/M12V: U1.33, U1#2.33
/MIXMODE: B12.3, F14.5
/PAGE2: C11.1, C12.5, F14.6, H1.10
/PISCA-PISCA: B3.3, B11.13, Q8.2
/PIXEL0: A3.12, A5.15
/PIXEL1: A3.11, A5.16
/PIXEL2: A3.10, A5.13
/PIXEL3: A3.5, A5.12
/PIXEL4: A3.4, A5.11
/Q3: C1.13, C2.9, C2.12, U1.37, U1#2.37
/RA0: E11.7, RA2.7, RA3.7, Z1.46
/RA1: E12.7, RA2.3, RA3.3, Z1.42
/RA2: E13.7, RA2.5, RA3.5, Z1.44
/RA3: E11.9, RA2.8, RA3.8, Z1.47
/RA4: E12.9, RA2.6, RA3.6, Z1.45
/RA5: E13.9, RA2.4, RA3.4, Z1.43
/RA6: C1.7, RA2.9, RA3.9, Z1.49
/RDY: H8.2, RA1.6, U1.21, U1#2.21
/RPULLUP_0: H12.6, JP1.2, RA1.7
/RPULLUP_1: D11.3, D12.3, D12.6, RA2.2
/R\~W: A2.4, C14.9, C14.13, H5.5, U1.18, U1#2.18
/SLOT_SELECT: U6.19, U7.19, U10.4, U10.5, U10.10
/SOFT5: A2.3, A2.8, A3.9, A5.27, A8.11, A10.1, A11.2, A11.3, A11.10, A11.13, B1.1, B2.4, B4.1, B5.1, B8.1, B9.1, B10.1, B10.4, B10.10, B10.12, C2.1, D11.1, D12.1, D13.1, D13.5, D14.1, D14.7, D14.10, E14.6, F3.27, F14.15, J13.1, J13.4, J13.10, J13.13, U4.1, U5.1
/SPK_OUT_CLK: F13.12, J13.3
/STROBE: A7.2, B10.11
/SYNC: C13.8, R8.2, U1.19, U1#2.19
/S_P1: A8.12, A10.4
/TEXTMODE: B13.11, F14.4, R27.1
/TEXT_VIDEO_SIGNAL: A9.3, A9.4, B2.11
/USER1: JP1.1, U1.39, U1#2.39
/V0: B14.9, D12.12, E11.4
/V1: B14.12, D12.11, E11.12
/V2: B12.4, C11.11, D11.14, E12.10
/V3: B11.9, D11.13, E14.7, E14.14
/V4: B11.10, B12.5, D11.12, E14.2, E14.11
/VA: A5.10, C12.3, D13.6, D13.11
/VB: A5.9, C12.6, D12.14
/VBL: B11.8, C13.13, C14.4
/VC: A5.8, A8.5, B14.8, C12.13, D12.13
/VIDEO_IS_TEXT: B5.3, B13.13
/VIDEO_SIGNAL: B10.5, R7.2
/auido_in: AUDIO2.T, kC10.2
/auido_out: AUDIO1.T, R18.2, R19.2
/gnd: U10.1, U10.7
/lA0: H5.12, H8.9
/lA1: H4.4, H8.10
/lA2: H5.6, H8.11
/lA3: H5.10, H8.12
/lA4: H4.6, H8.13
/lA5: H3.10, H8.14
/lA6: H3.12, H8.15
/lA7: H3.6, H8.16
/lA8: H3.4, H8.17
/lA9: H3.2, H8.18
/lA10: H4.10, H8.19
/lA11: H4.12, H8.20
/lA12: H4.2, H8.22
/lA13: H5.2, H8.23
/lA14: H5.14, H8.24
/lA15: H4.14, H8.25
/lD0: H8.33, H11.11
/lD1: H8.32, H11.12
/lD2: H8.31, H11.13
/lD3: H8.30, H11.14
/lD4: H8.29, H11.15
/lD5: H8.28, H11.16
/lD6: H8.27, H11.17
/lD7: H8.26, H11.18
/lR\~W: H5.4, H8.34
/lΦ0: B11.3, H8.37
/lΦ1: C14.10, H8.3
/pullup2: U10.2, U10.6, U10.8, U10.9
/~7M: A8.10, B1.13, B1.14, B12.9
/~CAS: B13.9, C2.13, F2.1
/~CAS_C: F2.4, Z1.23
/~CAS_D: F2.5, Z1.24
/~CAS_E: F2.6, Z1.25
/~CLRSTB: C11.3, F13.14
/~COLORREF: B1.2, B2.1, D2.2
/~DEVSEL: U1.41, U1#2.41
/~DEVSEL0: H2.15, U7.2
/~DEVSEL0': SLOTSCON1.8, U7.9, U7.18
/~DEVSEL1: H2.14, U7.4
/~DEVSEL1': SLOTSCON1.6, U7.7, U7.16
/~DEVSEL2: H2.13, U7.6
/~DEVSEL2': SLOTSCON1.4, U7.5, U7.14
/~DEVSEL3: H2.12, U7.8
/~DEVSEL3': SLOTSCON1.2, U7.3, U7.12
/~DEVSEL4: H2.11, U7.11
/~DEVSEL5: H2.10, U7.13
/~DEVSEL6: H2.9, U7.15
/~DEVSEL7: H2.7, U7.17
/~DMA: B11.1, C11.13, RA1.3, U1.22, U1#2.22
/~ENABLE_BUF: C11.12, H3.1, H3.15, H4.1, H4.15, H5.1, H5.15
/~ENABLE_IO: F13.5, H2.4, H12.15
/~EN_CASSETE_AND_JOY: F13.9, H14.7
/~EN_SOFTSWITCHES: F13.10, F14.14
/~H12_ENABLE: H12.4, H12.5, U102.8
/~HPE: B2.5, D13.9, D13.12, D14.9
/~INH: U1.32, U1#2.32
/~IOSEL0': SLOTSCON1.7, U6.9, U6.18
/~IOSEL1: H12.14, U6.4
/~IOSEL1': SLOTSCON1.5, U6.7, U6.16
/~IOSEL2: H12.13, U6.6
/~IOSEL2': SLOTSCON1.3, U6.5, U6.14
/~IOSEL3: H12.12, U6.8
/~IOSEL3': SLOTSCON1.1, U6.3, U6.12
/~IOSEL4: H12.11, U6.11
/~IOSEL5: H12.10, U6.13
/~IOSEL6: H12.9, U6.15
/~IOSEL7: H12.7, U6.17
/~IOSTB: U1.20, U1#2.20, U102.11
/~IRQ: H8.4, RA1.5, U1.30, U1#2.30
/~KBD: B6.1, B7.1, D2.13, F13.15
/~LPDS: A2.11, A3.15, D11.2, D12.2, D13.2, D14.2
/~MEMWR: C14.11, Z1.50
/~NMI: H8.6, RA1.4, U1.29, U1#2.29
/~PAGE2: C11.2, C12.2, C12.10
/~Q3: C1.11, C2.11
/~RAMSEL: A2.6, B6.15, B7.15
/~RAS: B5.9, B8.9, B13.8, C2.7, C2.15, U5.9, Z1.48
/~RESET: A7.3, H8.40, Q5.3, RA1.2, U1.31, U1#2.31
/~ROM_CS: F3.20, U101.11
/~SLOT_SELECT: U6.1, U7.1, U10.3
/~TEXT: A8.6, B5.2, B8.14
/Σ0: E12.12, E14.4
/Σ1: E12.6, E14.1
/Σ2: E13.6, E14.13
/Σ3: E13.10, E14.10
/Φ0: A2.12, B1.7, B11.2, B12.10, C1.2, D2.5, E11.14, E12.14, E13.14, F13.6, J1.1, U1.40, U1#2.40
/Φ1: B1.6, C14.12, H2.5, U1.38, U1#2.38, U100.1, U100.2
unnamed: A2.5, D2.8
unnamed: A3.13, B2.13
unnamed: A8.4, B4.7
unnamed: A8.9, B4.10, B9.10
unnamed: A9.5, B10.2
unnamed: A9.12, B9.13
unnamed: A9.14, B4.13
unnamed: A9.2, A9.15
unnamed: A8.7, A10.3
unnamed: A3.2, A10.6, B13.4
unnamed: A3.1, A10.12, B2.12
unnamed: A9.7, A10.13
unnamed: A9.11, A10.14
unnamed: A9.10, A10.15
unnamed: A9.9, A11.1, A12.13
unnamed: A8.1, A11.6
unnamed: A9.1, A11.9
unnamed: A12.1, B10.13
unnamed: A12.3, A13.3, R14.2
unnamed: A12.4, B14.11
unnamed: A12.5, A12.6, B14.10
unnamed: A12.10, A12.12
unnamed: A13.2, A13.6, R26.2, kC4.1
unnamed: B1.4, B2.3
unnamed: B1.5, B1.10, C1.10, C1.12
unnamed: B1.12, C1.9
unnamed: B2.6, D2.1
unnamed: B2.9, Q2.3, R3.1
unnamed: B3.2, B3.6, R13.2, kC15.1
unnamed: B3.7, R12.2, R13.1
unnamed: B8.3, B8.15
unnamed: B11.11, B13.5
unnamed: B12.1, B13.1
unnamed: B12.6, B13.12
unnamed: B12.12, R5.2
unnamed: B13.3, C13.10, Q7.3, R35.1
unnamed: B14.1, C13.1
unnamed: B14.2, B14.4
unnamed: B14.3, C11.10
unnamed: B14.13, C13.12
unnamed: C1.5, C12.12
unnamed: C1.6, C12.9
unnamed: C2.5, D2.6
unnamed: C11.6, E14.12, E14.15
unnamed: C11.8, D11.9, D12.9
unnamed: C11.9, D11.15
unnamed: C12.4, E11.6
unnamed: C12.7, E11.10
unnamed: C14.8, H11.1
unnamed: CR1.1, Q4.2, R24.1
unnamed: CRYSTAL1.1, Q1.3, R2.1
unnamed: CRYSTAL1.2, Q2.2, R4.1
unnamed: D2.9, F2.10
unnamed: D2.10, F2.11
unnamed: D2.12, F2.12
unnamed: D11.4, D11.5, D11.7, D11.10, D12.15
unnamed: D12.5, D12.7, D12.10, D13.15
unnamed: D13.7, D13.10, D14.15
unnamed: F2.3, F2.13, J1.12
unnamed: F2.2, F2.14, J1.9
unnamed: F3.1, U4.2
unnamed: H1.8, J1.11
unnamed: H13.4, kC9.1
unnamed: J13.2, J13.6
unnamed: J13.8, J13.12
unnamed: J14.4, R22.2
unnamed: J14.5, R20.2
unnamed: J14.8, R21.2
unnamed: J14.9, R23.2
unnamed: K13.2, R17.1, R30.1
unnamed: K13.3, R15.1, R16.1
unnamed: K13.6, R15.2, R29.1
unnamed: Q1.1, Q2.1, R1.2
unnamed: Q3.1, R11.1
unnamed: Q3.2, R6.1, R7.1, R8.1
unnamed: Q3.3, R9.2
unnamed: Q4.3, R25.2
unnamed: Q5.2, R14.1
unnamed: Q6.2, R27.2
unnamed: Q7.2, R33.2, R34.2
unnamed: Q9.3, Q10.3
unnamed: R10.1, VIDEOCON1.1
unnamed: R10.2, R11.2
unnamed: R24.2, kC11.1
unnamed: R25.1, SPK1.2, kC12.1
unnamed: R30.2, kC10.1
unnamed: RSTR1.1, U3.3
unnamed: U1.1, U1#2.1
unnamed: U1.23, U1#2.23
unnamed: U1.24, U1#2.24
unnamed: U1.27, U1#2.27
unnamed: U1.28, U1#2.28
unnamed: U1.50, U1#2.50
unnamed: U2.1, U3.2
unnamed: U100.3, U100.4
unnamed: U100.8, U101.1, U101.2, U102.5
unnamed: U100.9, U100.11
unnamed: U100.6, U100.12, U100.13
unnamed: U101.8, U102.12
unnamed: U101.12, U102.6, U102.10, U102.13
unnamed: U101.3, U101.13
unnamed: U102.3, U102.4
